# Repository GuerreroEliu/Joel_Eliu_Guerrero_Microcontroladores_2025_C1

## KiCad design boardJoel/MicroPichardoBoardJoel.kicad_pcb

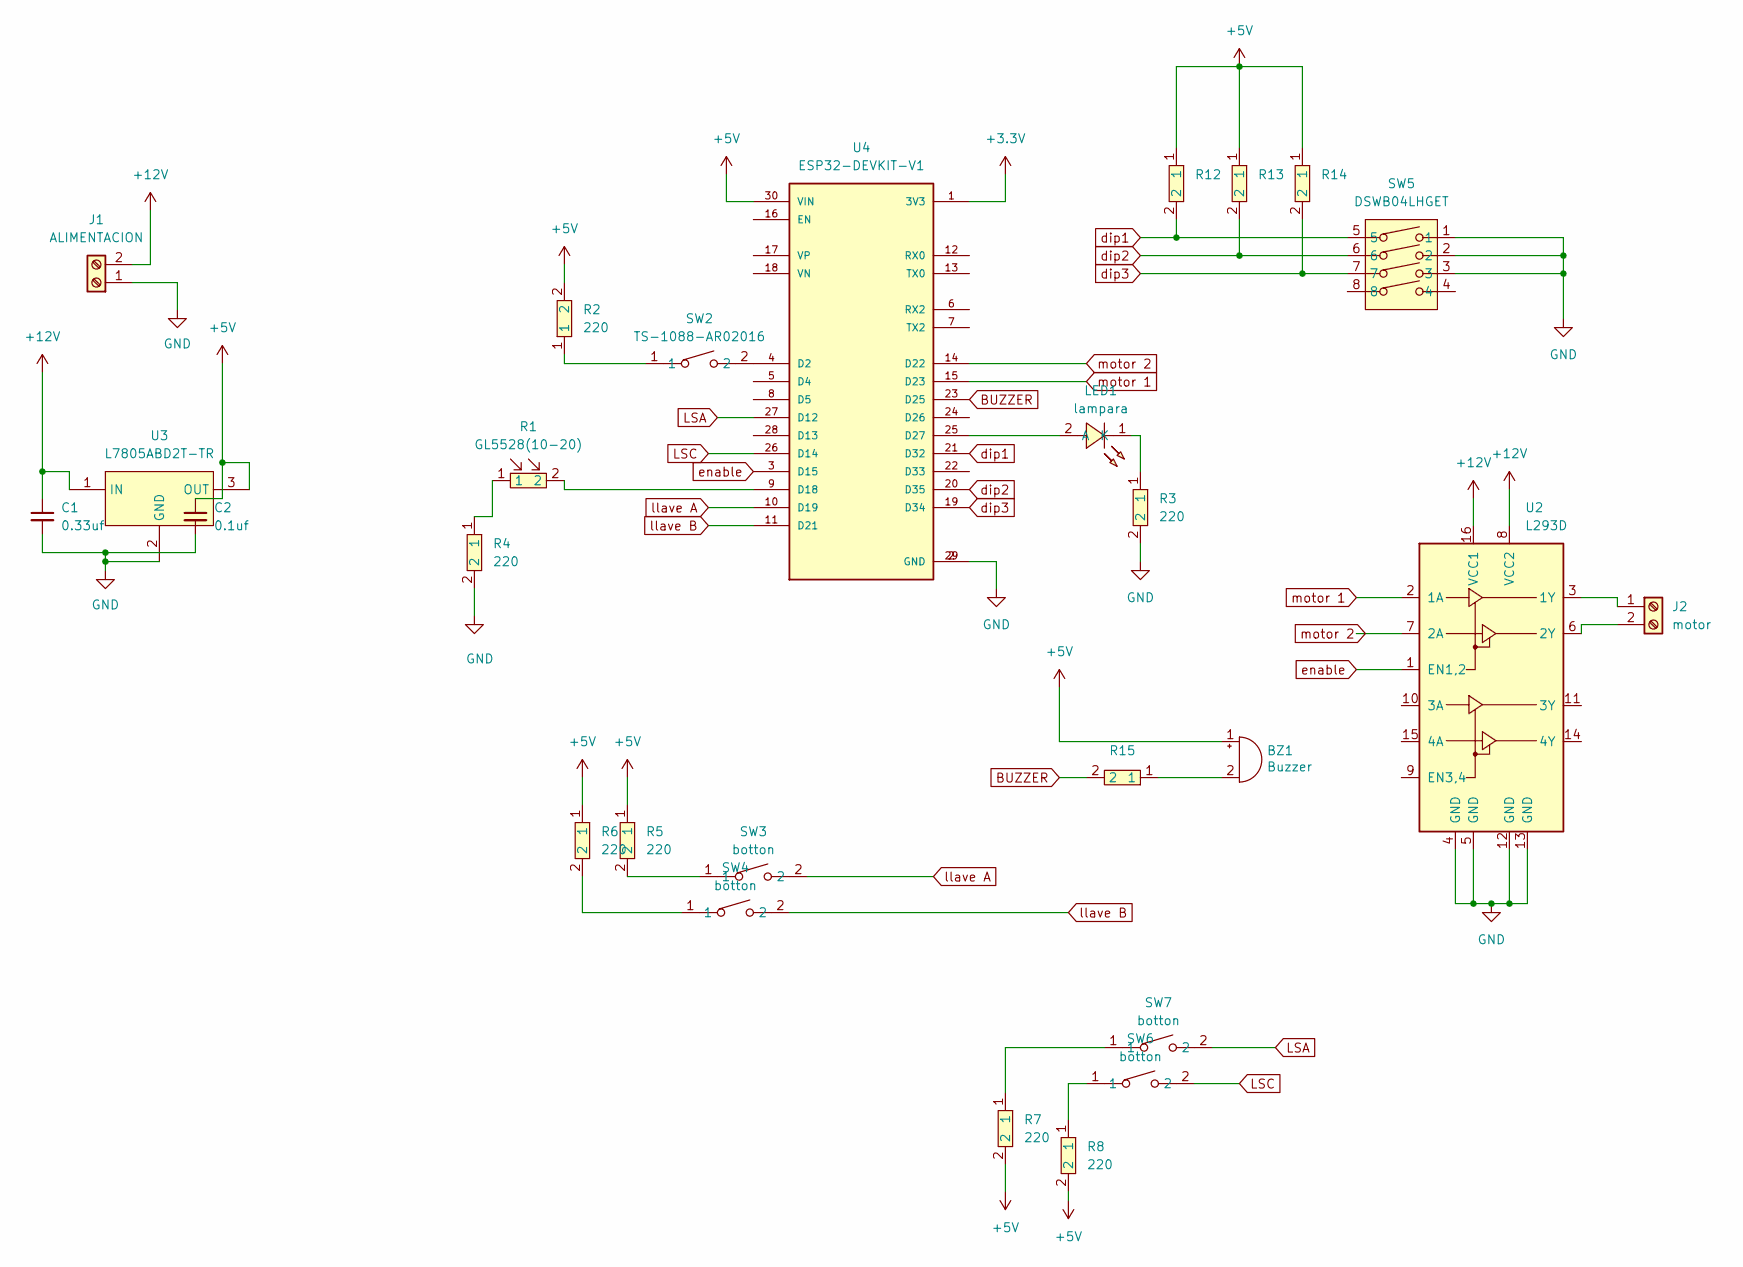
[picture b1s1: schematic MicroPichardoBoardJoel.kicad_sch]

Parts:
BZ1: Buzzer; Buzzer_CUI_CPT-9019S-SMT
C1: 0.33uf; C_0402_1005Metric
C2: 0.1uf; C_0402_1005Metric
J1: ALIMENTACION; TerminalBlock_bornier-2_P5.08mm
J2: motor; TerminalBlock_bornier-2_P5.08mm
LED1: lampara; LED0603-RD_RED; LCSC Part C965799
R1: GL5528(10-20); RES-TH_L5.1-W4.3-P3.40-D0.5; LCSC Part C10081
R2, R3, R4, R5, R6, R7, R8: 220; R1206; LCSC Part C25363
R12, R13, R14, R15: RC1206FR-071KL; R1206; LCSC Part C131398
SW2: TS-1088-AR02016; SW-SMD_L3.9-W3.0-P4.45; LCSC Part C720477
SW3, SW4, SW6, SW7: botton; SW-SMD_L3.9-W3.0-P4.45; LCSC Part C720477
SW5: DSWB04LHGET; SW-TH_DSWB04LHGET; LCSC Part C99418
U2: L293D; DIP-16_W7.62mm_Socket
U3: L7805ABD2T-TR; TO-263-2_L10.0-W9.2-P5.08-LS15.3-TL-CW; LCSC Part C86206
U4: ESP32-DEVKIT-V1; MODULE_ESP32_DEVKIT_V1; PARTREV N/A

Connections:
+3.3V: U4.1 (3V3)
+5V: BZ1.1 (+), C2.1, R2.2, R5.1, R6.1, R7.2, R8.2, R12.1, R13.1, R14.1, U3.3 (OUT), U4.30 (VIN)
+12V: C1.1, J1.2, U2.8 (VCC2), U2.16 (VCC1), U3.1 (IN)
BUZZER: R15.2, U4.23 (D25)
GND: C1.2, C2.2, J1.1, R3.2, R4.2, SW5.1, SW5.2, SW5.3, U2.4 (GND), U2.5 (GND), U2.12 (GND), U2.13 (GND), U3.2 (GND), U4.2 (GND), U4.29 (GND)
LSA: SW7.2, U4.27 (D12)
LSC: SW6.2, U4.26 (D14)
unnamed: BZ1.2 (-), R15.1
unnamed: J2.1, U2.3 (1Y)
unnamed: J2.2, U2.6 (2Y)
unnamed: LED1.2 (A), U4.25 (D27)
unnamed: LED1.1 (K), R3.1
unnamed: R1.1, R4.1
unnamed: R2.1, SW2.1
unnamed: R5.2, SW3.1
unnamed: R6.2, SW4.1
unnamed: R7.1, SW7.1
unnamed: R8.1, SW6.1
unnamed: SW2.2, U4.4 (D2)
unnamed: R1.2, U4.9 (D18)
dip1: R12.2, SW5.5, U4.21 (D32)
dip2: R13.2, SW5.6, U4.20 (D35)
dip3: R14.2, SW5.7, U4.19 (D34)
enable: U2.1 (EN1,2), U4.3 (D15)
llave A: SW3.2, U4.10 (D19)
llave B: SW4.2, U4.11 (D21)
motor 1: U2.2 (1A), U4.15 (D23)
motor 2: U2.7 (2A), U4.14 (D22)

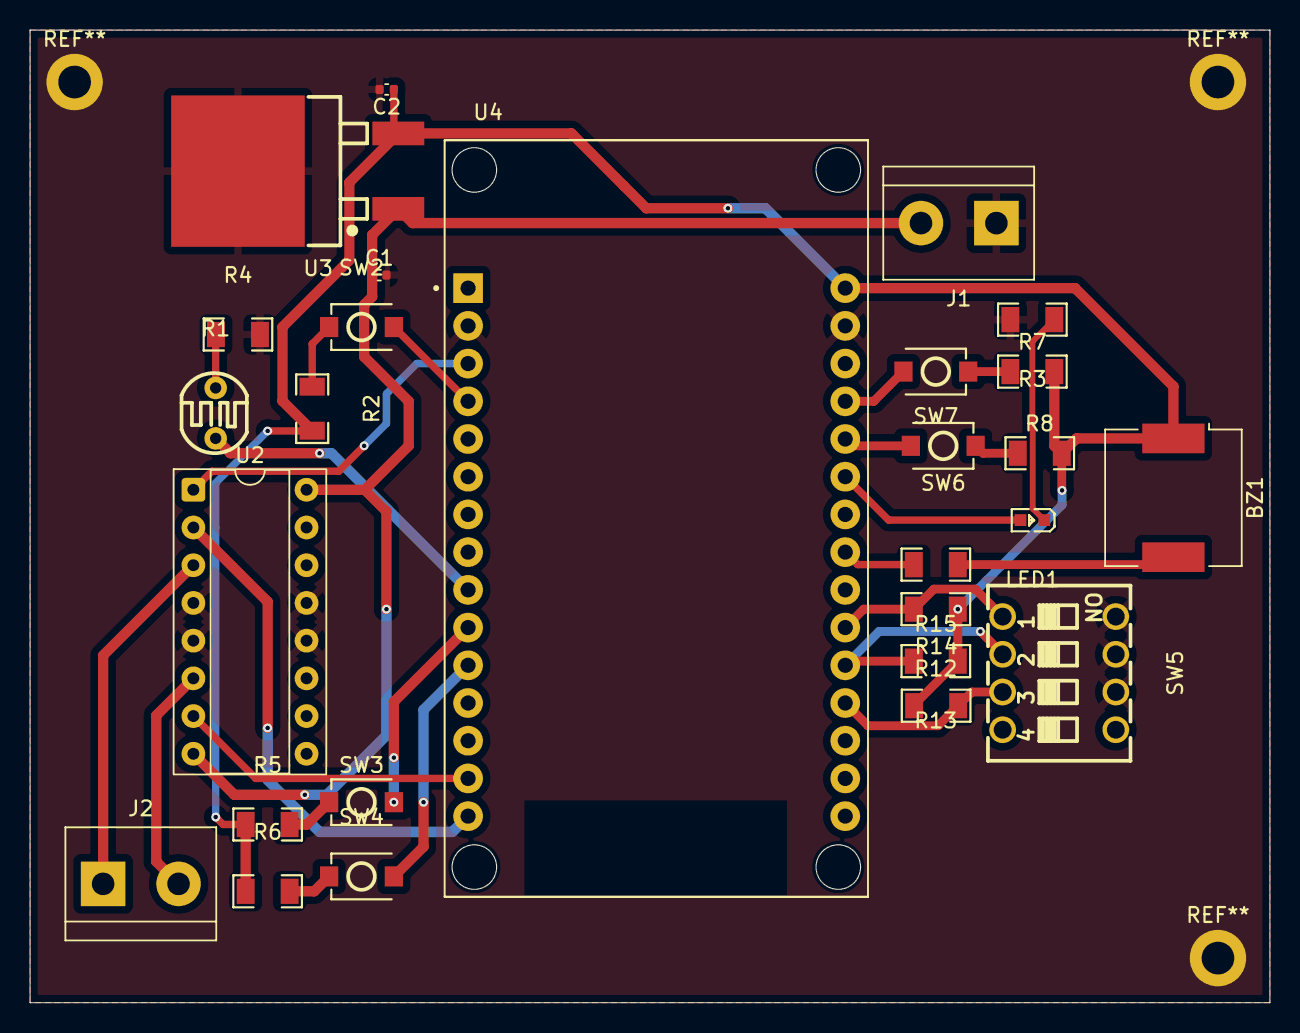
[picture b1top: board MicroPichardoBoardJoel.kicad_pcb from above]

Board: 2 copper layers, 83.5 x 65.5 mm, 27 parts (0 on the bottom side), 27 nets.

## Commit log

2025-01-31 hola feliz año
2025-01-31 Resumen
2025-01-31 tarea 1
2025-02-14 maquina de estado
2025-02-14 maquina a mano
2025-02-15 protocolos de automatización industrial
2025-03-26 parcial 2
2025-03-26 Delete parcial 2 pulsación del led directory
    Delete parcial 2 pulsación del led directory
2025-03-26 2do parcial
2025-04-10 boardmicro
2025-04-25 tarea 4
2025-04-25 finalmicro
2025-04-26 proyectofinalM
2025-04-29 Create tarea 4
